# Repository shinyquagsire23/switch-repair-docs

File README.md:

# switch-repair-docs

This repository contains (WIP) documentation on Switch PCBs, components, etc for the purpose of refurbishing and repair.

## T210 Ballout
See [here](https://docs.google.com/spreadsheets/d/1iTGRDA_61uCa7ii975vWkOaQfZ4wij3pMzxb2HG2QLY/edit?usp=sharing)

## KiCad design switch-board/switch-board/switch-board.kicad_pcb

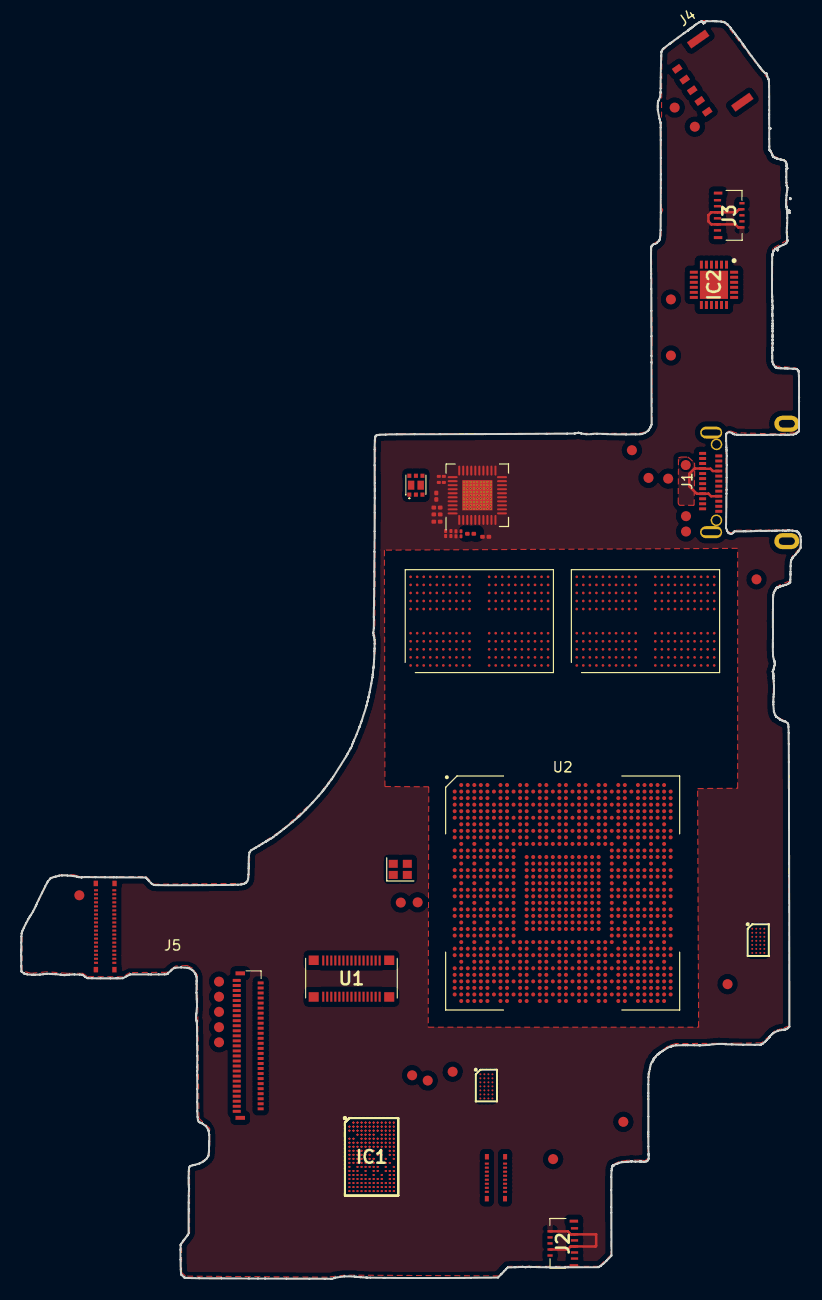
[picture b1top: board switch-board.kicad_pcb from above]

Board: 12 copper layers, 77.4 x 124.9 mm, 36 parts (0 on the bottom side), 23 nets.

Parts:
C1, C2, C3, C4, C6, C7: C; C_0201_0603Metric
C5: C; C_01005_0402Metric
IC1: CYW4356XKWBG; BGA192C40P12X18_487X767X55
IC2: BQ24193RGET; QFN50P400X400X100-25N-D
IC**: WLP-HC-28
IC**#2: WLP-HC-28
IC**#3: BGA192C40P12X18_487X767X55
J1: USB_C_Receptacle; switch_usb
J2, J3: 503566-1102; 5035661102
J4: BATT; BM05B-ACHSS
J5: switch_lcd; 046844753002846_copy
J5#2: switch_lcd; lcd_molex
J**: SD; sd_molex
J**#2: GC; 5024304030_copy
Q**: SSM6P49NULF
R1, R2, R3, R4, R5: R_US; R_01005_0402Metric
TP1: VBUS; switch_TestPoint_Pad_D1.0mm
TP2, TP4, TP5: TestPoint; switch_TestPoint_Pad_D1.0mm
TP3: VBAT; switch_TestPoint_Pad_D1.0mm
TP6: USB_D-; switch_TestPoint_Pad_D1.0mm
TP7: USB_D+; switch_TestPoint_Pad_D1.0mm
U1: switch_mmc; 5009130302
U2: t210
U3: M92T36; QFN-40_EP_5.9x5.9_Pitch0.4mm

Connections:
GND: C1.2, C2.1, C3.2, C4.2, C5.2, C7.1, IC2.17, IC2.18, IC2.19, IC2.20, IC2.25, J2.4, J2.5, J2.9, J2.10, J3.4, J3.5, J3.9, J3.10, R5.2
unnamed: C1.1, U3.39
unnamed: C2.2, U3.40
unnamed: C3.1, U3.41
unnamed: C4.1, U3.36
unnamed: C5.1, R4.1
unnamed: C6.1, U3.5
unnamed: C6.2, R1.2, R2.2, R3.2, R4.2
unnamed: C7.2, U3.6
unnamed: IC2.1, IC2.24
unnamed: IC2.12, TP2.1
unnamed: IC2.15, IC2.16
unnamed: J1.A1, J1.A12, J1.B1, J1.B12
unnamed: J1.A6, J1.B6, TP7.1
unnamed: J1.A7, J1.B7, TP6.1
unnamed: J4.1, J4.2, TP4.1
unnamed: J4.3, TP5.1
unnamed: R1.1, U3.31
unnamed: R2.1, U3.32
unnamed: R3.1, U3.2
unnamed: R5.1, U3.3
VBAT: IC2.13, J4.4, J4.5, TP3.1
VBUS: J1.A4, J1.A9, J1.B4, J1.B9, TP1.1

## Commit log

2021-05-01 More datasheets
2021-05-01 Add ballout note
